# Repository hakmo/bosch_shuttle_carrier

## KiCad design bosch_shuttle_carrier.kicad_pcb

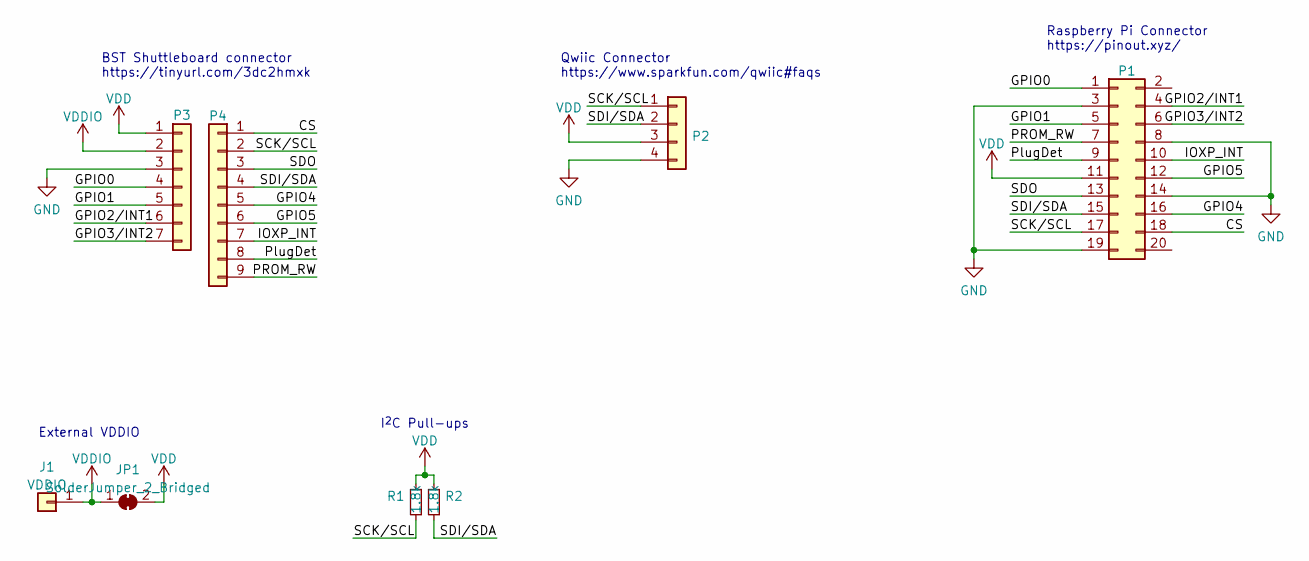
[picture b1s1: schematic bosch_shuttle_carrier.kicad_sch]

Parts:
J1: VDDIO; PinHeader_1x01_P2.54mm_Vertical
JP1: SolderJumper_2_Bridged; SolderJumper-2_P1.3mm_Bridged_RoundedPad1.0x1.5mm
P1: Raspberry Pi Connector; PinSocket_2x10_P2.54mm_Vertical
P2: Qwiic Connector; JST_SH_BM04B-SRSS-TB_1x04-1MP_P1.00mm_Vertical
P3: Conn_01x07; PinSocket_1x07_P1.27mm_Vertical
P4: Conn_01x09; PinSocket_1x09_P1.27mm_Vertical
R1, R2: 1.8k; R_0805_2012Metric_Pad1.20x1.40mm_HandSolder

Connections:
/CS: P1.18, P4.1
/GPIO0: P1.1, P3.4
/GPIO1: P1.5, P3.5
/GPIO2/INT1: P1.4, P3.6
/GPIO3/INT2: P1.6, P3.7
/GPIO4: P1.16, P4.5
/GPIO5: P1.12, P4.6
/IOXP_INT: P1.10, P4.7
/PROM_RW: P1.7, P4.9
/PlugDet: P1.9, P4.8
/SCK/SCL: P1.17, P2.1, P4.2, R1.2
/SDI/SDA: P1.15, P2.2, P4.4, R2.2
/SDO: P1.13, P4.3
GND: P1.3, P1.8, P1.14, P1.19, P2.4, P3.3
VDD: JP1.2 (B), P1.11, P2.3, P3.1, R1.1, R2.1
VDDIO: J1.1, JP1.1 (A), P3.2

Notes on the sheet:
Raspberry Pi Connector https://pinout.xyz/
External VDDIO
I^{2}C Pull-ups
BST Shuttleboard connector https://tinyurl.com/3dc2hmxk
Qwiic Connector https://www.sparkfun.com/qwiic#faqs

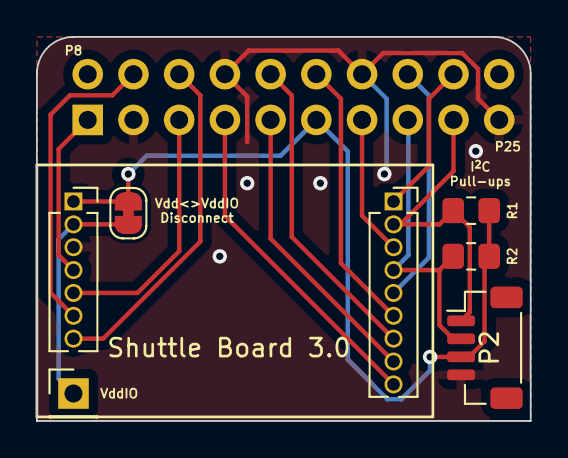
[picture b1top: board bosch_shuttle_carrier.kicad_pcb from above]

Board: 2 copper layers, 27.4 x 21.3 mm, 8 parts (1 on the bottom side), 16 nets.

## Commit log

2023-02-28 Board rev1
2023-03-11 Add schematics v1.0 board
